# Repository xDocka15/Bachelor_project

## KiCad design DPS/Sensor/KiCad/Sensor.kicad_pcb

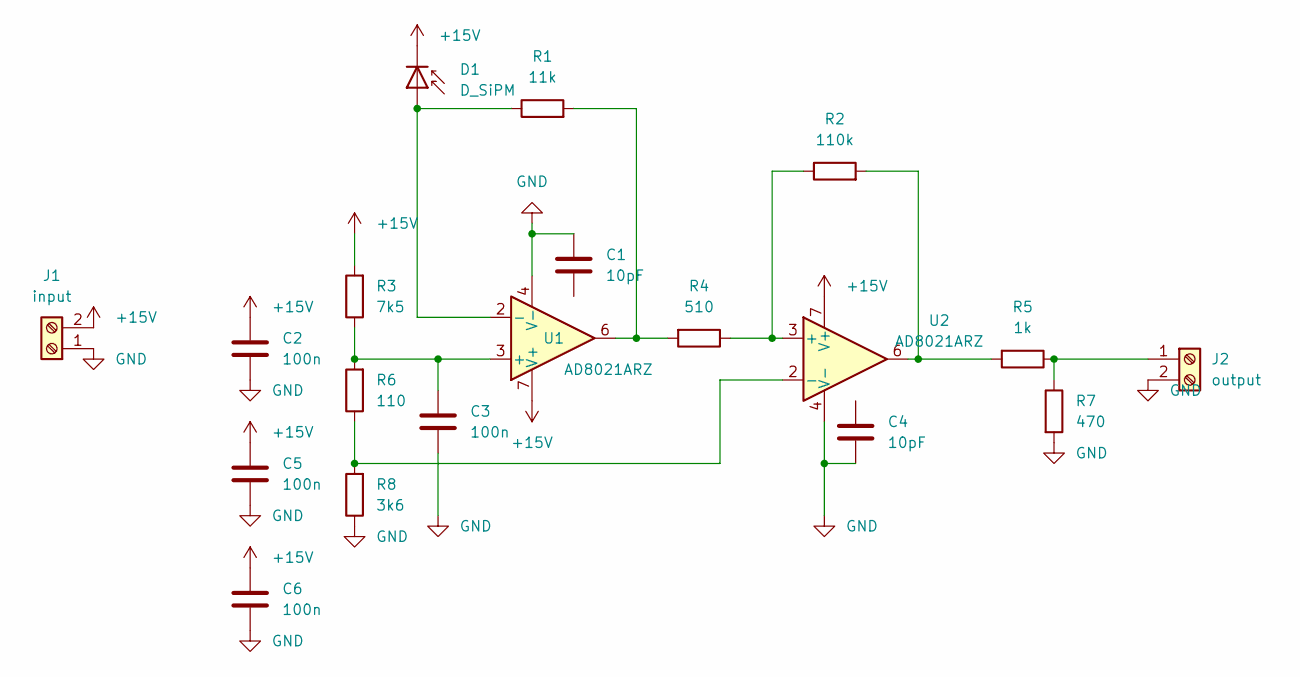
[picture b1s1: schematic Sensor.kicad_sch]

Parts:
C1, C4: 10pF; C_0805_2012Metric_Pad1.18x1.45mm_HandSolder
C2, C3, C5, C6: 100n; C_1210_3225Metric_Pad1.33x2.70mm_HandSolder
D1: D_SiPM; LED_D1.8mm_W3.3mm_H2.4mm
J1: input; PinHeader_1x02_P2.54mm_Vertical
J2: output; PinHeader_1x02_P2.54mm_Vertical
R1: 11k; R_1206_3216Metric_Pad1.30x1.75mm_HandSolder
R2: 110k; R_1206_3216Metric_Pad1.30x1.75mm_HandSolder
R3: 7k5; R_1206_3216Metric_Pad1.30x1.75mm_HandSolder
R4: 510; R_1206_3216Metric_Pad1.30x1.75mm_HandSolder
R5: 1k; R_1206_3216Metric_Pad1.30x1.75mm_HandSolder
R6: 110; R_1206_3216Metric_Pad1.30x1.75mm_HandSolder
R7: 470; R_1206_3216Metric_Pad1.30x1.75mm_HandSolder
R8: 3k6; R_1206_3216Metric_Pad1.30x1.75mm_HandSolder
U1, U2: AD8021ARZ; SOIC-8_3.9x4.9mm_P1.27mm

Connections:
+15V: C2.1, C5.1, C6.1, D1.1 (K), J1.2, R3.2, U1.7 (V+), U2.7 (V+)
GND: C1.1, C2.2, C3.2, C4.2, C5.2, C6.2, J1.1, J2.2, R7.2, R8.1, U1.4 (V-), U2.4 (V-)
unnamed: C3.1, R3.1, R6.2, U1.3 (+)
unnamed: D1.2 (A), R1.1, U1.2 (-)
unnamed: J2.1, R5.1, R7.1
unnamed: R1.2, R4.2, U1.6
unnamed: R2.1, R4.1, U2.3 (+)
unnamed: R2.2, R5.2, U2.6
unnamed: R6.1, R8.2, U2.2 (-)

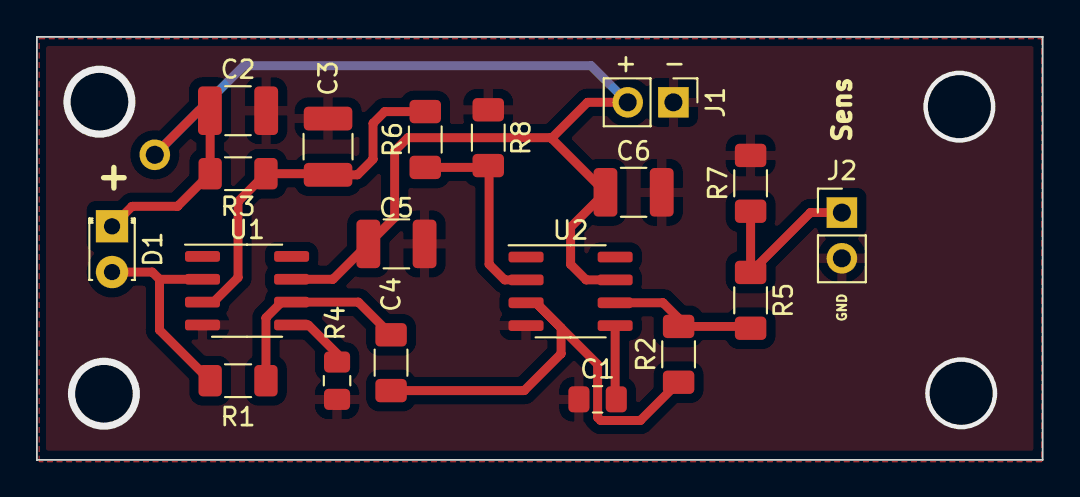
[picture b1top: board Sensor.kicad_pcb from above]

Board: 2 copper layers, 55.9 x 23.5 mm, 19 parts (0 on the bottom side), 9 nets.

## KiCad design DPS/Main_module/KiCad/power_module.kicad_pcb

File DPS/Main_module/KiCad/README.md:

V návrhu DPS nejsou provedeny změny popsané v kapitole 3.5.2

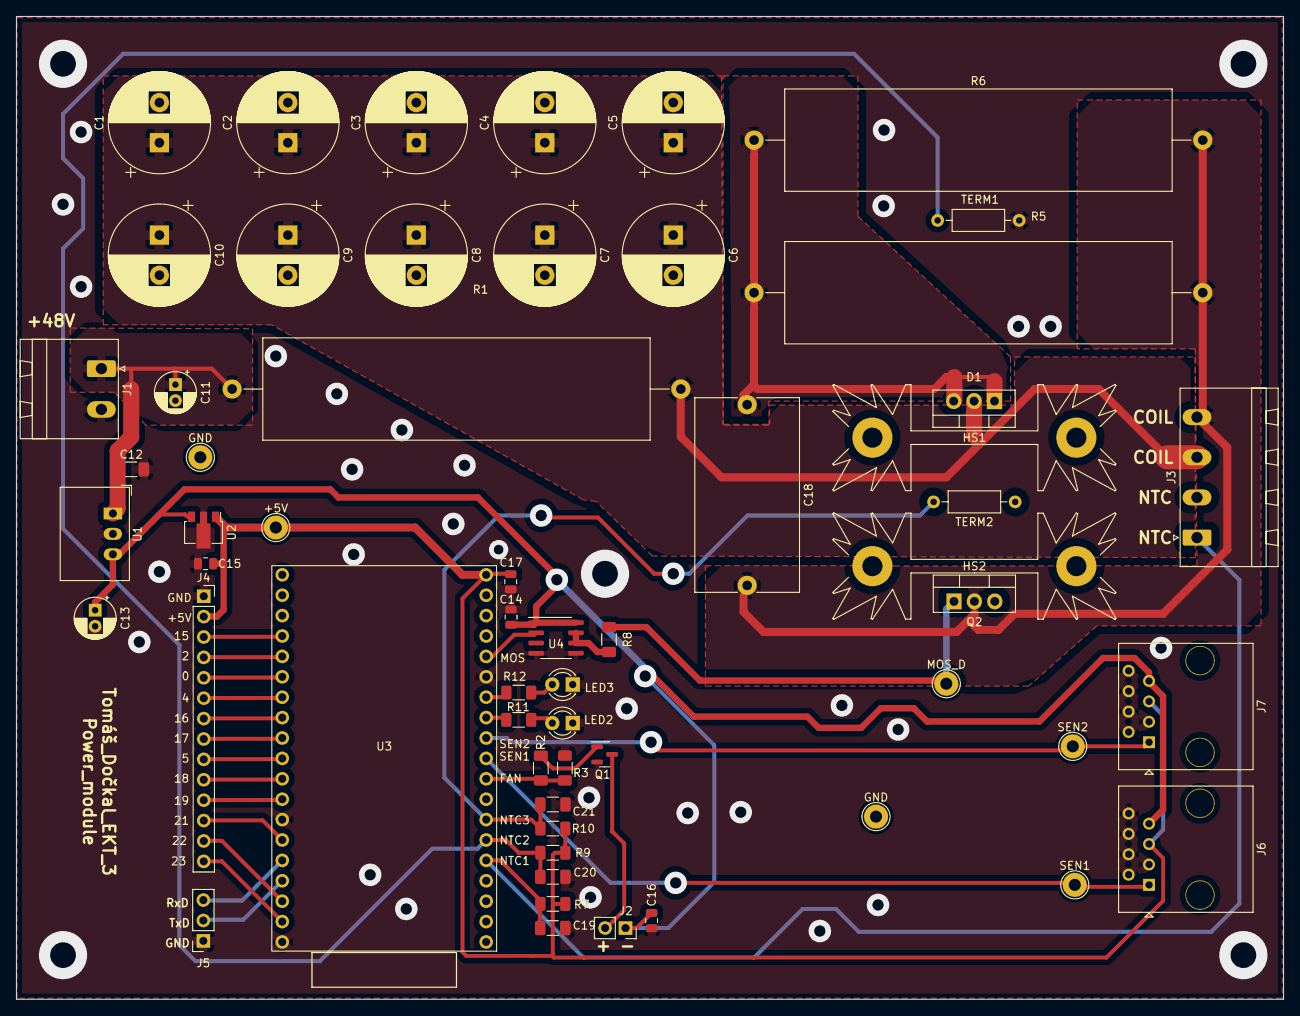
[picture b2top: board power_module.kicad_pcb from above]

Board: 2 copper layers, 157.8 x 122.4 mm, 58 parts (0 on the bottom side), 36 nets.

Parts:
+5V: TestPoint_THTPad_D3.0mm_Drill1.5mm
C1, C2, C3, C4, C5, C6, C7, C8, C9, C10: 560uF; CP_Radial_D12.5mm_P5.00mm
C11, C13: 10uF; CP_Radial_D5.0mm_P2.00mm
C12, C19, C20, C21: 100nF; C_1206_3216Metric_Pad1.33x1.80mm_HandSolder
C14, C15, C16, C17: 100nF; C_0805_2012Metric
C18: 2uF; C_Rect_L24.0mm_W12.8mm_P22.50mm_MKT
D1: MBR30150CT; TO-220-3_Vertical
GND: TestPoint_THTPad_D3.0mm_Drill1.5mm
GND#2: TestPoint_THTPad_D3.0mm_Drill1.5mm
HS1: Heatsink_D1; Heatsink_Fischer_SK104-STC-STIC_35x13mm_2xDrill2.5mm
HS2: Heatsink_MOS; Heatsink_Fischer_SK104-STC-STIC_35x13mm_2xDrill2.5mm
J1: +48V; PhoenixContact_MSTBA_2,5_2-G-5,08_1x02_P5.08mm_Horizontal
J2: FAN; PinSocket_1x02_P2.54mm_Vertical
J3: COIL+NTC; PhoenixContact_MSTBA_2,5_4-G_1x04_P5.00mm_Horizontal
J4: Display; PinSocket_1x14_P2.54mm_Vertical
J5: UART; PinSocket_1x03_P2.54mm_Vertical
J6, J7: RJ45; RJ45_OST_PJ012-8P8CX_Vertical
LED2, LED3: LED; LED_D3.0mm
MOS_D: TestPoint_THTPad_D3.0mm_Drill1.5mm
Q1: Q_NMOS_GDS; SOT-23
Q2: IXFP60N25X3; TO-220-3_Vertical
R1: 4R7; R_Axial_Power_L48.0mm_W12.5mm_P55.88mm
R2, R8: 10; R_1206_3216Metric_Pad1.30x1.75mm_HandSolder
R3: 100k; R_1206_3216Metric_Pad1.30x1.75mm_HandSolder
R5, R6: 10; R_Axial_Power_L48.0mm_W12.5mm_P55.88mm
R7, R9, R10: 4k7; R_1206_3216Metric_Pad1.30x1.75mm_HandSolder
R11, R12: 67R; R_1206_3216Metric_Pad1.30x1.75mm_HandSolder
SEN1, SEN2: TestPoint_THTPad_D3.0mm_Drill1.5mm
TERM1, TERM2: 100k; R_Axial_DIN0207_L6.3mm_D2.5mm_P10.16mm_Horizontal
U1: AMSRU-7815JZ; Converter_DCDC_RECOM_R-78HB-0.5_THT
U2: MC78L05ACHT1G; SOT-89-3
U3: esp32; ESP32
U4: MCP14A0302-E/SN; SOIC-8_3.9x4.9mm_P1.27mm

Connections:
+5V: +5V.1, C15.1, C17.1, J4.2, J6.5, J7.5, R7.2, R9.2, R10.2, U2.1 (OUT), U3.19 (5V)
+15V: C13.1, C14.1, C16.1, J2.1, J6.7, J7.7, U1.3 (OUT), U2.3 (IN), U4.1 (VDD), U4.8 (VDD)
+48V: C11.1, C12.1, J1.1, R1.1, U1.1 (IN)
COIL1: C1.1, C2.1, C3.1, C4.1, C5.1, C6.1, C7.1, C8.1, C9.1, C10.1, D1.2 (K), J3.3, R1.2
COIL2: C18.2, J3.4, Q2.2 (D), R5.2, R6.2
FAN-: J2.2, Q1.3 (D)
FAN_PWM: R2.1, R3.1, U3.9 (1025)
LED_1: R11.1, U3.12 (1014)
LED_2: R12.1, U3.13 (1012)
MOS: U3.15 (1013), U4.2 (IN)
NTC1: C19.1, J3.1, R7.1, U3.5 (1034)
NTC1_2: C1.2, C2.2, C3.2, C4.2, C5.2, C6.2, C7.2, C8.2, C9.2, C10.2, C11.2, C12.2, C13.2, C14.2, C15.2, C16.2, C17.2, C19.2, C20.2, C21.2, J1.2, J3.2, J4.1, J5.1, J6.2, J6.3, J6.4, J6.6, J6.8, J7.2, J7.3, J7.4, J7.6, J7.8, LED2.1 (K), LED3.1 (K), Q1.2 (S), Q2.3 (S), R3.2, TERM1.2, TERM2.2, U1.2 (GND), U2.2 (GND), U3.14 (GND), U3.20 (GND), U3.26 (GND), U4.4 (GND), U4.5 (GND)
NTC2: C20.1, R9.1, TERM1.1, U3.6 (1035)
NTC3: C21.1, R10.1, TERM2.1, U3.7 (1032)
unnamed: C18.1, D1.1 (A1), D1.3 (A2), R5.1, R6.1
unnamed: J4.3, U3.35 (1015)
unnamed: J4.4, U3.34 (102)
unnamed: J4.5, U3.33 (100)
unnamed: J4.6, U3.32 (104)
unnamed: J4.7, U3.31 (1016)
unnamed: J4.8, U3.30 (1017)
unnamed: J4.9, U3.29 (105)
unnamed: J4.10, U3.28 (1018)
unnamed: J4.11, U3.27 (1019)
unnamed: J4.12, U3.25 (1021)
unnamed: J4.13, U3.22 (1022)
unnamed: J4.14, U3.21 (1023)
unnamed: J5.2, U3.23 (TXD)
unnamed: J5.3, U3.24 (RXD)
unnamed: LED2.2 (A), R11.2
unnamed: LED3.2 (A), R12.2
unnamed: Q1.1 (G), R2.2
unnamed: MOS_D.1, Q2.1 (G), R8.2
unnamed: R8.1, U4.6 (OUT), U4.7 (OUT)
Sensor_1: J6.1, SEN1.1, U3.10 (1026)
Sensor_2: J7.1, SEN2.1, U3.11 (1027)

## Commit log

2022-10-27 sem file upload
2023-04-16 synch
2023-04-23 main upd
2023-06-06 mains
2023-06-15 bug fixes
2023-12-19 latest
2024-08-05 updated esp
2024-08-05 added .zip
2024-08-05 added 3D, DPS, Matlab
2024-08-05 added .zip file
